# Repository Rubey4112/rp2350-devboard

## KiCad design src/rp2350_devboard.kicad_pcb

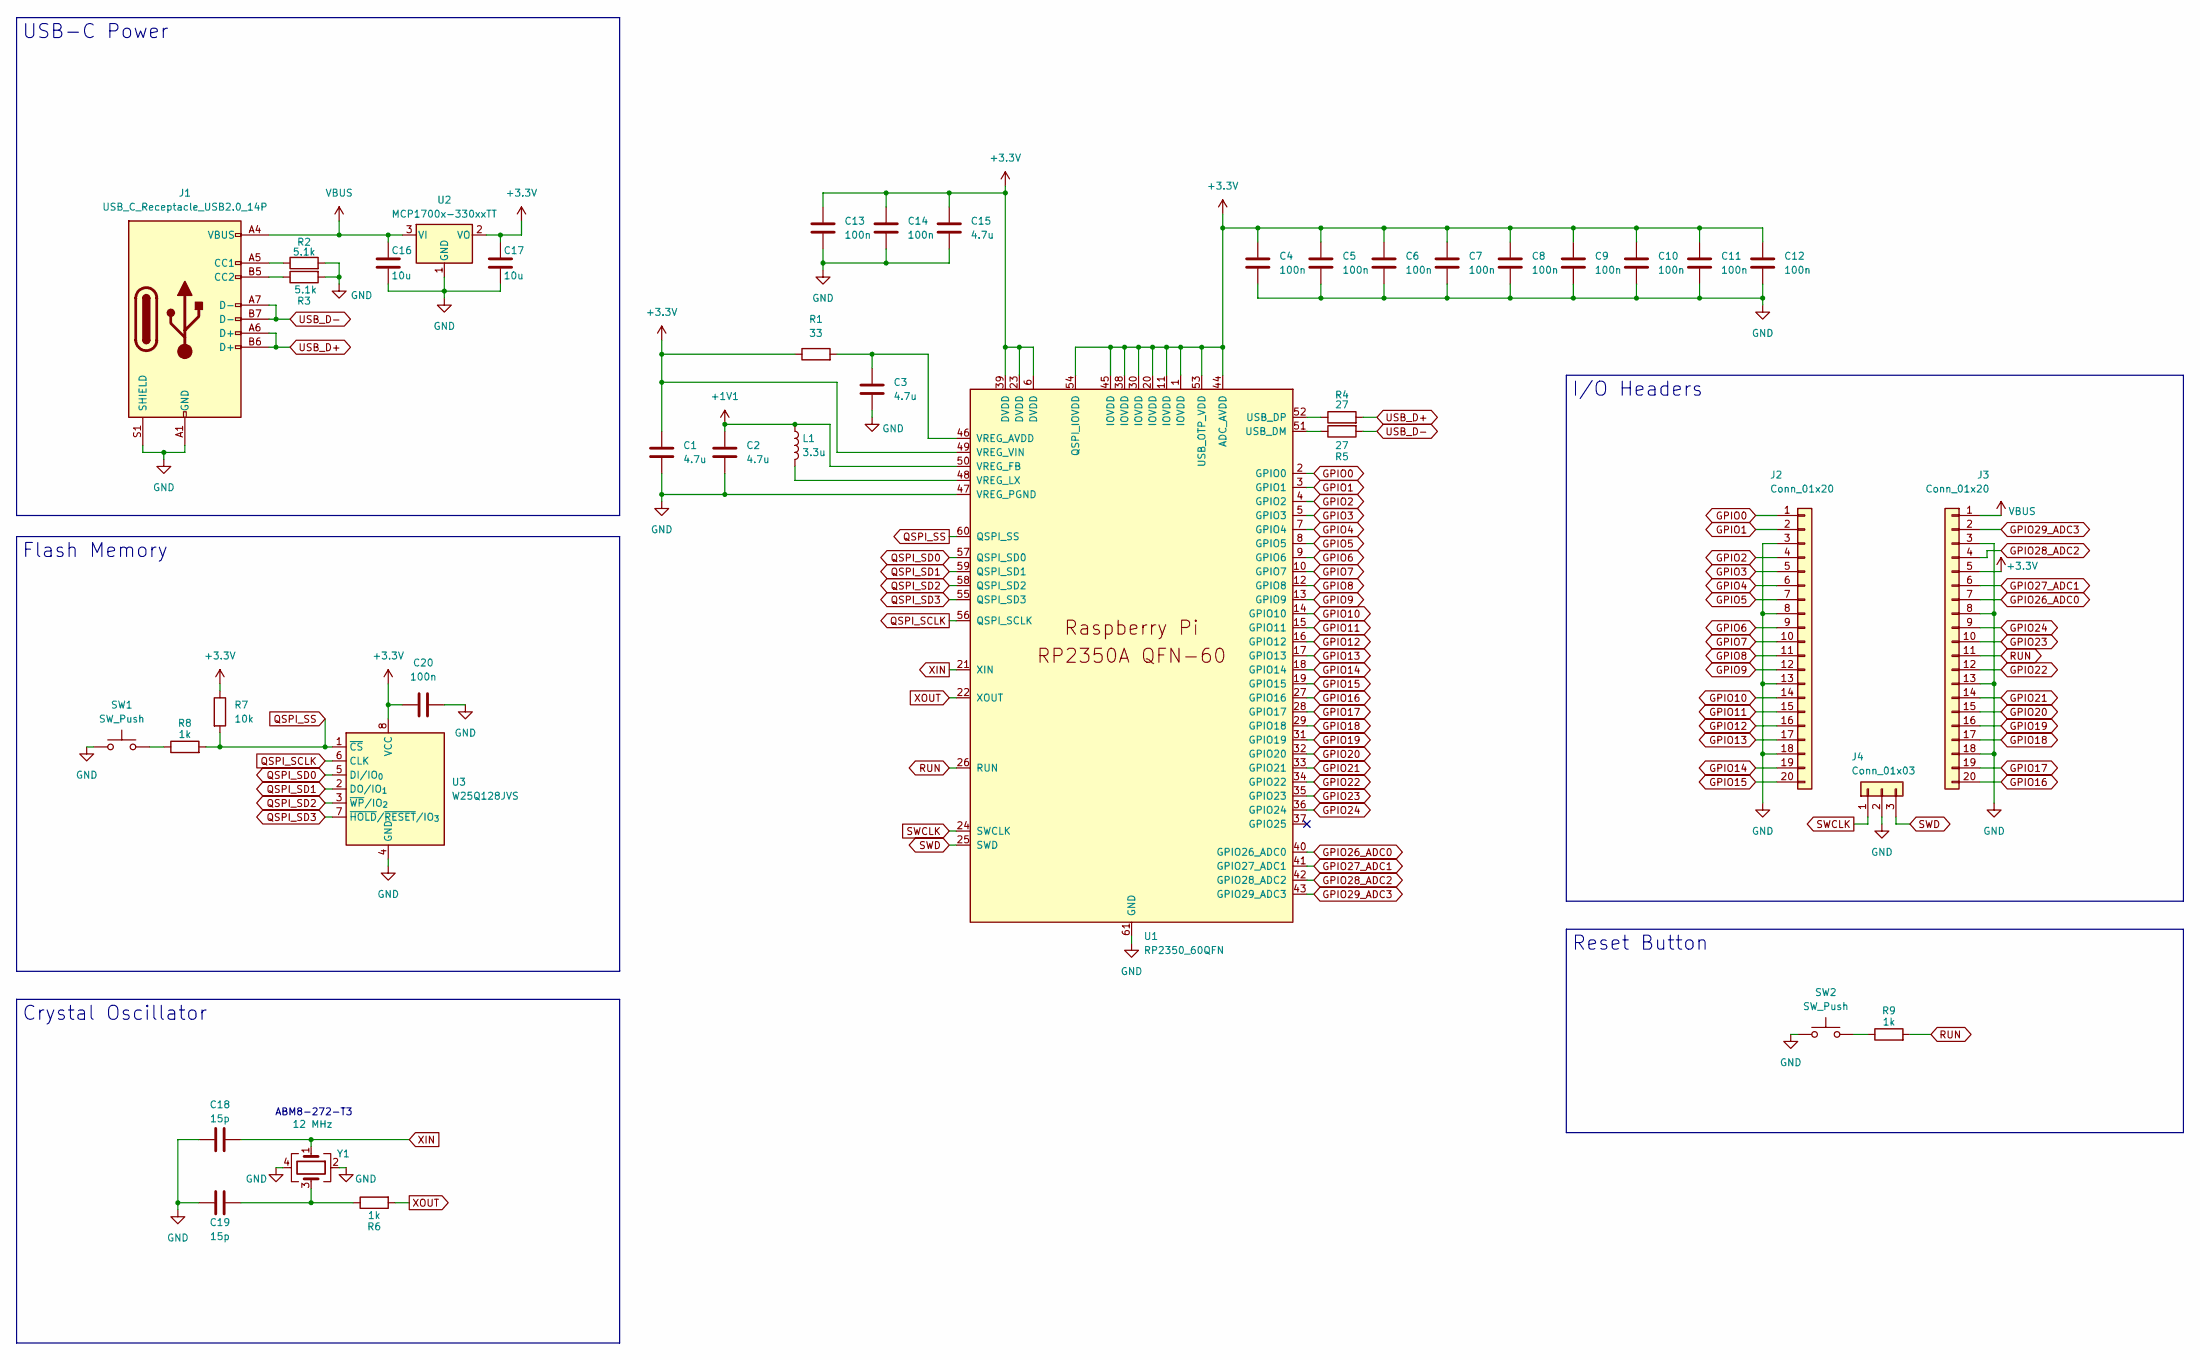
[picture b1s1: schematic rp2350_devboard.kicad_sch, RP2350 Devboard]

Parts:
C1, C2, C3, C15: 4.7u; C_0402_1005Metric
C4, C5, C6, C7, C8, C9, C10, C11, C12, C13, C14, C20: 100n; C_0402_1005Metric
C16, C17: 10u; C_0603_1608Metric
C18, C19: 15p; C_0402_1005Metric
J1: USB_C_Receptacle_USB2.0_14P; USB_C_Receptacle_HRO_TYPE-C-31-M-12
J2, J3: Conn_01x20; PinHeader_1x20_P2.54mm_Vertical
J4: Conn_01x03; PinHeader_1x03_P2.54mm_Vertical
L1: 3.3u; L_pol_2016
R1: 33; R_0402_1005Metric
R2, R3: 5.1k; R_0402_1005Metric
R4, R5: 27; R_0402_1005Metric
R6, R8, R9: 1k; R_0402_1005Metric
R7: 10k; R_0402_1005Metric
SW1, SW2: SW_Push; SW_Push_SPST_NO_Alps_SKRK
U1: RP2350_60QFN; RP2350-QFN-60-1EP_7x7_P0.4mm_EP3.4x3.4mm_ThermalVias
U2: MCP1700x-330xxTT; SOT-23
U3: W25Q128JVS; SOIC-8_5.3x5.3mm_P1.27mm
Y1: 12 MHz; Crystal_SMD_3225-4Pin_3.2x2.5mm

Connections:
+1V1: C2.1, L1.1, U1.50 (VREG_FB)
+3.3V: C1.1, C4.1, C5.1, C6.1, C7.1, C8.1, C9.1, C10.1, C11.1, C12.1, C13.1, C14.1, C15.1, C17.1, C20.1, J3.5, R1.1, R7.1, U1.1 (IOVDD), U1.6 (DVDD), U1.11 (IOVDD), U1.20 (IOVDD), U1.23 (DVDD), U1.30 (IOVDD), U1.38 (IOVDD), U1.39 (DVDD), U1.44 (ADC_AVDD), U1.45 (IOVDD), U1.49 (VREG_VIN), U1.53 (USB_OTP_VDD), U1.54 (QSPI_IOVDD), U2.2 (VO), U3.8 (VCC)
GND: C1.2, C2.2, C3.2, C4.2, C5.2, C6.2, C7.2, C8.2, C9.2, C10.2, C11.2, C12.2, C13.2, C14.2, C15.2, C16.2, C17.2, C18.2, C19.2, C20.2, J1.A1 (GND), J1.A12 (GND), J1.B1 (GND), J1.B12 (GND), J1.S1 (SHIELD), J2.3, J2.8, J2.13, J2.18, J3.3, J3.8, J3.13, J3.18, J4.2, R2.2, R3.2, SW1.1, SW2.1, U1.47 (VREG_PGND), U1.61 (GND), U2.1 (GND), U3.4 (GND), Y1.2, Y1.4
GPIO0: J2.1, U1.2 (GPIO0)
GPIO1: J2.2, U1.3 (GPIO1)
GPIO2: J2.4, U1.4 (GPIO2)
GPIO3: J2.5, U1.5 (GPIO3)
GPIO4: J2.6, U1.7 (GPIO4)
GPIO5: J2.7, U1.8 (GPIO5)
GPIO6: J2.9, U1.9 (GPIO6)
GPIO7: J2.10, U1.10 (GPIO7)
GPIO8: J2.11, U1.12 (GPIO8)
GPIO9: J2.12, U1.13 (GPIO9)
GPIO10: J2.14, U1.14 (GPIO10)
GPIO11: J2.15, U1.15 (GPIO11)
GPIO12: J2.16, U1.16 (GPIO12)
GPIO13: J2.17, U1.17 (GPIO13)
GPIO14: J2.19, U1.18 (GPIO14)
GPIO15: J2.20, U1.19 (GPIO15)
GPIO16: J3.20, U1.27 (GPIO16)
GPIO17: J3.19, U1.28 (GPIO17)
GPIO18: J3.17, U1.29 (GPIO18)
GPIO19: J3.16, U1.31 (GPIO19)
GPIO20: J3.15, U1.32 (GPIO20)
GPIO21: J3.14, U1.33 (GPIO21)
GPIO22: J3.12, U1.34 (GPIO22)
GPIO23: J3.10, U1.35 (GPIO23)
GPIO24: J3.9, U1.36 (GPIO24)
GPIO26_ADC0: J3.7, U1.40 (GPIO26_ADC0)
GPIO27_ADC1: J3.6, U1.41 (GPIO27_ADC1)
GPIO28_ADC2: J3.4, U1.42 (GPIO28_ADC2)
GPIO29_ADC3: J3.2, U1.43 (GPIO29_ADC3)
unnamed: C19.1, R6.1, Y1.3
unnamed: J1.A5 (CC1), R2.1
unnamed: J1.B5 (CC2), R3.1
unnamed: R8.1, SW1.2
unnamed: R9.1, SW2.2
unnamed: R5.1, U1.51 (USB_DM)
unnamed: R4.1, U1.52 (USB_DP)
unnamed: C3.1, R1.2, U1.46 (VREG_AVDD)
unnamed: L1.2, U1.48 (VREG_LX)
QSPI_SCLK: U1.56 (QSPI_SCLK), U3.6 (CLK)
QSPI_SD0: U1.57 (QSPI_SD0), U3.5 (DI/IO_{0})
QSPI_SD1: U1.59 (QSPI_SD1), U3.2 (DO/IO_{1})
QSPI_SD2: U1.58 (QSPI_SD2), U3.3 (~WP/IO_{2})
QSPI_SD3: U1.55 (QSPI_SD3), U3.7 (~HOLD/~RESET/IO_{3})
QSPI_SS: R7.2, R8.2, U1.60 (QSPI_SS), U3.1 (~CS)
RUN: J3.11, R9.2, U1.26 (RUN)
SWCLK: J4.1, U1.24 (SWCLK)
SWD: J4.3, U1.25 (SWD)
USB_D+: J1.A6 (D+), J1.B6 (D+), R4.2
USB_D-: J1.A7 (D-), J1.B7 (D-), R5.2
VBUS: C16.1, J1.A4 (VBUS), J1.A9 (VBUS), J1.B4 (VBUS), J1.B9 (VBUS), J3.1, U2.3 (VI)
XIN: C18.1, U1.21 (XIN), Y1.1
XOUT: R6.2, U1.22 (XOUT)

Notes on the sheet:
ABM8-272-T3
Flash Memory
Reset Button
I/O Headers
USB-C Power
Crystal Oscillator

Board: 2 copper layers, 40 parts (0 on the bottom side), 55 nets, no tracks yet.

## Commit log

2025-10-05 RP2350 Power Routing
2025-10-06 Schematic finished
2025-10-07 Assigned all footprints
